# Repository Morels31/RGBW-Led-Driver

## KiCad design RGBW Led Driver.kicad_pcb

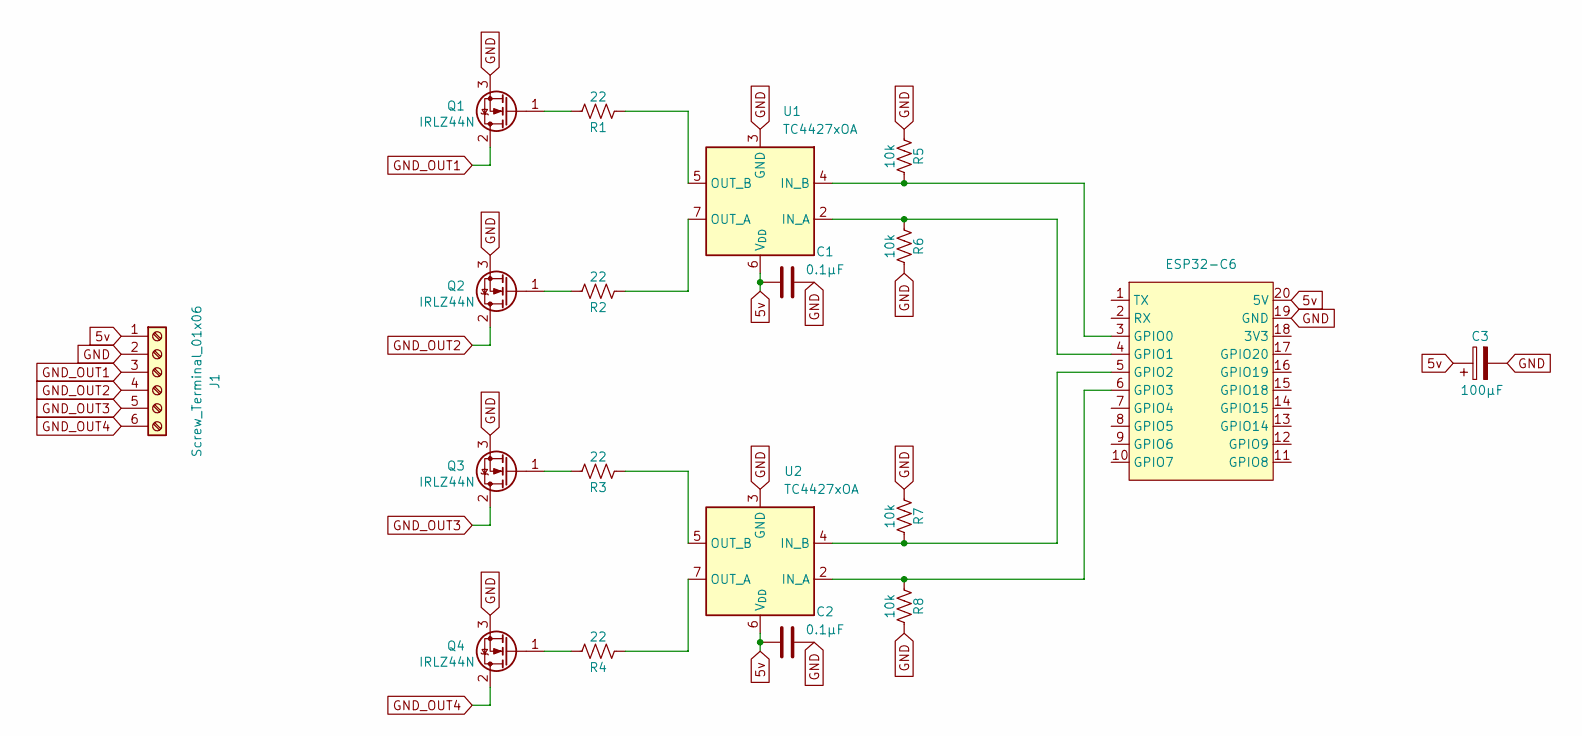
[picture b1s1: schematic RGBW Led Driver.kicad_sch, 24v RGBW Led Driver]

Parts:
C1, C2: 0.1µF; C_Axial_L3.8mm_D2.6mm_P7.50mm_Horizontal
C3: 100µF; CP_Radial_D6.3mm_P2.50mm
D1: ESP32-C6; ESP32-C6 Supermini
J1: Screw_Terminal_01x06; TerminalBlock_Phoenix_MKDS-1,5-6-5.08_1x06_P5.08mm_Horizont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
Q1, Q2, Q3, Q4: IRLZ44N; TO-220-3_Vertical
R1, R2, R3, R4: 22; R_Axial_DIN0204_L3.6mm_D1.6mm_P7.62mm_Horizontal
R5, R6, R7, R8: 10k; R_Axial_DIN0204_L3.6mm_D1.6mm_P7.62mm_Horizontal
U1, U2: TC4427xOA; DIP-8_W7.62mm

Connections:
5v: C1.1, C2.1, C3.1, D1.20 (5V), J1.1, U1.6 (V_{DD}), U2.6 (V_{DD})
GND: C1.2, C2.2, C3.2, D1.19 (GND), J1.2, Q1.3 (S), Q2.3 (S), Q3.3 (S), Q4.3 (S), R5.2, R6.2, R7.2, R8.2, U1.3 (GND), U2.3 (GND)
GND_OUT1: J1.3, Q1.2 (D)
GND_OUT2: J1.4, Q2.2 (D)
GND_OUT3: J1.5, Q3.2 (D)
GND_OUT4: J1.6, Q4.2 (D)
unnamed: D1.3 (GPIO0), R5.1, U1.4 (IN_B)
unnamed: D1.4 (GPIO1), R6.1, U1.2 (IN_A)
unnamed: D1.5 (GPIO2), R7.1, U2.4 (IN_B)
unnamed: D1.6 (GPIO3), R8.1, U2.2 (IN_A)
unnamed: Q1.1 (G), R1.2
unnamed: Q2.1 (G), R2.2
unnamed: Q3.1 (G), R3.2
unnamed: Q4.1 (G), R4.2
unnamed: R2.1, U1.7 (OUT_A)
unnamed: R1.1, U1.5 (OUT_B)
unnamed: R4.1, U2.7 (OUT_A)
unnamed: R3.1, U2.5 (OUT_B)

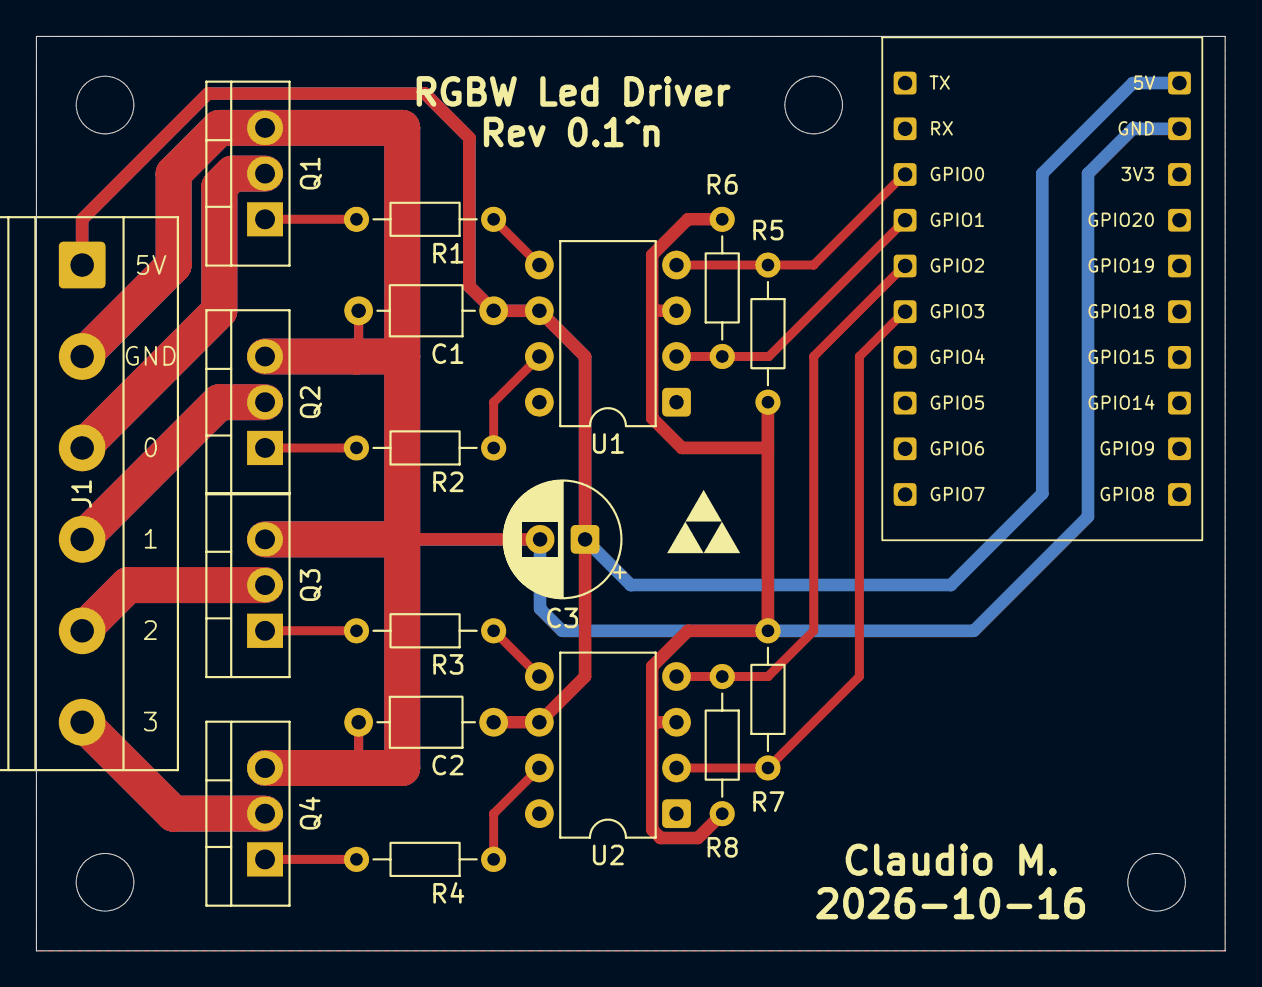
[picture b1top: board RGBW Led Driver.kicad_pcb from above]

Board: 2 copper layers, 66.0 x 50.8 mm, 19 parts (0 on the bottom side), 18 nets.
